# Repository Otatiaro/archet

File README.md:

# Archet

Open-source debug and production-test probe, and hardware-in-the-loop (HIL) platform.

- SWD and JTAG with **reliable simultaneous SWO**, on separate hardware paths;
- ARM, RISC-V and ESP32 (Xtensa) targets;
- USB HS (USB-C, PD) and 100 Mbit/s Ethernet with PoE+, IEEE 1588 clock synchronisation;
- HIL platform: real-time rules on raw IOs (≤ 1 µs), edge timestamping, safe state; each project only adds a simple shield, or [Bornier](https://github.com/bornier-dev/bornier) modules;
- host side: probe-rs, CMSIS-DAP v2 compatibility, Rust/Python library and MCP server.

Built around an STM32H723 and a Lattice iCE40UP5K, manufacturable at JLCPCB with no BGA.

**Status:** architecture draft, no hardware yet.

## Documentation

- [Architecture](docs/architecture.md): goals, decisions, block diagram, MCU ↔ FPGA link, power, pinout constraints, sourcing and cost.

## Related projects

- [OpSy](https://github.com/Otatiaro/OpSy): firmware runtime (C++26);
- [SvdGenerator](https://github.com/Otatiaro/SvdGenerator): register headers;
- [Bornier](https://github.com/bornier-dev/bornier): DIN-rail IO modules, shared local bus.

## Contributing

All content in this repository is in English: code, comments, documentation, commit messages and pull requests.

## License

[MIT](LICENSE), hardware, gateware, firmware and software alike.

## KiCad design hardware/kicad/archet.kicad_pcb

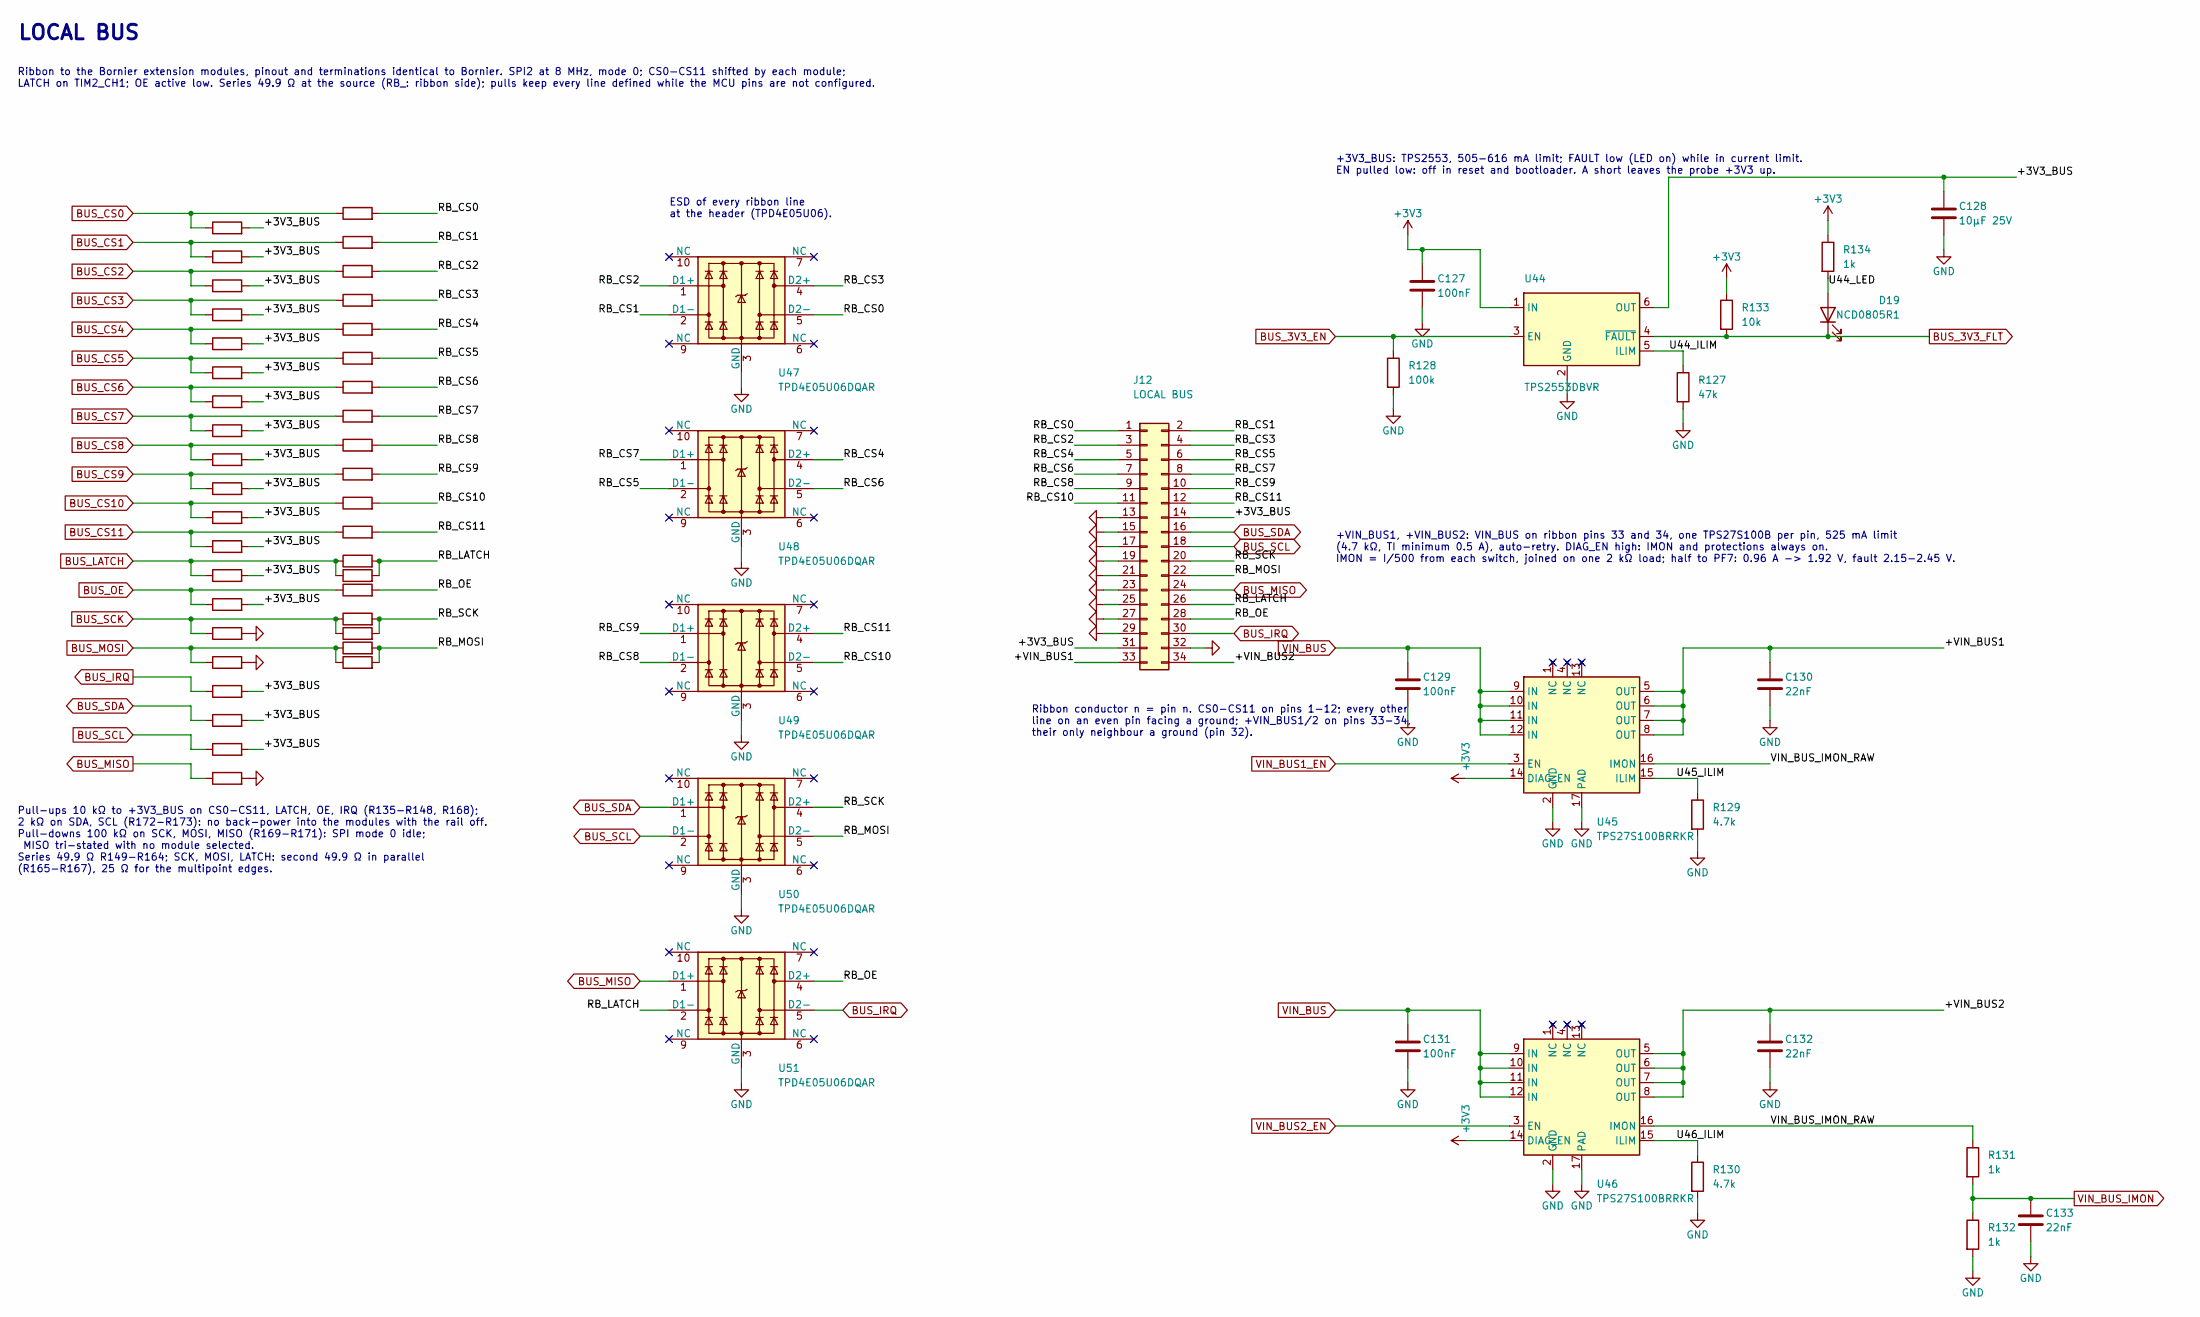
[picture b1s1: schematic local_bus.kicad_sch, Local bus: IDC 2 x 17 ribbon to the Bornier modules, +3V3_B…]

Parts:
C127, C129, C131: 100nF; C_0402_1005Metric; LCSC C307331
C128: 10µF 25V; C_0805_2012Metric; LCSC C15850
C130, C132, C133: 22nF; C_0402_1005Metric; LCSC C1532
D19: NCD0805R1; LED_0805_2012Metric; LCSC C84256
J12: LOCAL BUS; IDC-Header_2x17_P2.54mm_Vertical; LCSC C20920
R127: 47k; R_0402_1005Metric; LCSC C25792
R128, R169, R170, R171: 100k; R_0402_1005Metric; LCSC C25741
R129, R130: 4.7k; R_0402_1005Metric; LCSC C25900
R131, R132, R134: 1k; R_0402_1005Metric; LCSC C11702
R133, R135, R136, R137, R138, R139, R140, R141, R142, R143, R144, R145, R146, R147, R148, R168: 10k; R_0402_1005Metric; LCSC C25744
R149, R150, R151, R152, R153, R154, R155, R156, R157, R158, R159, R160, R161, R162, R163, R164, R165, R166, R167: 49.9; R_0402_1005Metric; LCSC C25120
R172, R173: 2k; R_0402_1005Metric; LCSC C4109
U44: TPS2553DBVR; SOT-23-6; LCSC C55266
U45, U46: TPS27S100BRRKR; Texas_RRK0016A_WQFN-16-1EP_3.5x4mm_P0.5mm_EP2.05x2.55mm; LCSC C1849486
U47, U48, U49, U50, U51: TPD4E05U06DQAR; USON-10_2.5x1.0mm_P0.5mm; LCSC C138714

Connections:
+3V3: C127.1, R133.1, R134.1, U44.1 (IN), U45.14 (DIAG_EN), U46.14 (DIAG_EN); also elsewhere on the board
/Local bus/+3V3_BUS: C128.1, J12.14, J12.31, R135.2, R136.2, R137.2, R138.2, R139.2, R140.2, R141.2, R142.2, R143.2, R144.2, R145.2, R146.2, R147.2, R148.2, R168.2, R172.2, R173.2, U44.6 (OUT)
/Local bus/+VIN_BUS1: C130.1, J12.33, U45.5 (OUT), U45.6 (OUT), U45.7 (OUT), U45.8 (OUT)
/Local bus/+VIN_BUS2: C132.1, J12.34, U46.5 (OUT), U46.6 (OUT), U46.7 (OUT), U46.8 (OUT)
/Local bus/RB_CS0: J12.1, R149.2, U47.5 (D2-)
/Local bus/RB_CS1: J12.2, R150.2, U47.2 (D1-)
/Local bus/RB_CS2: J12.3, R151.2, U47.1 (D1+)
/Local bus/RB_CS3: J12.4, R152.2, U47.4 (D2+)
/Local bus/RB_CS4: J12.5, R153.2, U48.4 (D2+)
/Local bus/RB_CS5: J12.6, R154.2, U48.2 (D1-)
/Local bus/RB_CS6: J12.7, R155.2, U48.5 (D2-)
/Local bus/RB_CS7: J12.8, R156.2, U48.1 (D1+)
/Local bus/RB_CS8: J12.9, R157.2, U49.2 (D1-)
/Local bus/RB_CS9: J12.10, R158.2, U49.1 (D1+)
/Local bus/RB_CS10: J12.11, R159.2, U49.5 (D2-)
/Local bus/RB_CS11: J12.12, R160.2, U49.4 (D2+)
/Local bus/RB_LATCH: J12.26, R163.2, R167.2, U51.2 (D1-)
/Local bus/RB_MOSI: J12.22, R162.2, R166.2, U50.5 (D2-)
/Local bus/RB_OE: J12.28, R164.2, U51.4 (D2+)
/Local bus/RB_SCK: J12.20, R161.2, R165.2, U50.4 (D2+)
/Local bus/U44_ILIM: R127.1, U44.5 (ILIM)
/Local bus/U44_LED: D19.2 (A), R134.2
/Local bus/U45_ILIM: R129.1, U45.15 (ILIM)
/Local bus/U46_ILIM: R130.1, U46.15 (ILIM)
/Local bus/VIN_BUS_IMON_RAW: R131.1, U45.16 (IMON), U46.16 (IMON)
BUS_3V3_EN: R128.1, U44.3 (EN); also elsewhere on the board
BUS_3V3_FLT: D19.1 (K), R133.2, U44.4 (~FAULT); also elsewhere on the board
BUS_CS0: R135.1, R149.1; also elsewhere on the board
BUS_CS1: R136.1, R150.1; also elsewhere on the board
BUS_CS2: R137.1, R151.1; also elsewhere on the board
BUS_CS3: R138.1, R152.1; also elsewhere on the board
BUS_CS4: R139.1, R153.1; also elsewhere on the board
BUS_CS5: R140.1, R154.1; also elsewhere on the board
BUS_CS6: R141.1, R155.1; also elsewhere on the board
BUS_CS7: R142.1, R156.1; also elsewhere on the board
BUS_CS8: R143.1, R157.1; also elsewhere on the board
BUS_CS9: R144.1, R158.1; also elsewhere on the board
BUS_CS10: R145.1, R159.1; also elsewhere on the board
BUS_CS11: R146.1, R160.1; also elsewhere on the board
BUS_IRQ: J12.30, R168.1, U51.5 (D2-); also elsewhere on the board
BUS_LATCH: R147.1, R163.1, R167.1; also elsewhere on the board
BUS_MISO: J12.24, R169.1, U51.1 (D1+); also elsewhere on the board
BUS_MOSI: R162.1, R166.1, R171.1; also elsewhere on the board
BUS_OE: R148.1, R164.1; also elsewhere on the board
BUS_SCK: R161.1, R165.1, R170.1; also elsewhere on the board
BUS_SCL: J12.18, R173.1, U50.2 (D1-); also elsewhere on the board
BUS_SDA: J12.16, R172.1, U50.1 (D1+); also elsewhere on the board
GND: C127.2, C128.2, C129.2, C130.2, C131.2, C132.2, C133.2, J12.13, J12.15, J12.17, J12.19, J12.21, J12.23, J12.25, J12.27, J12.29, J12.32, R127.2, R128.2, R129.2, R130.2, R132.2, R169.2, R170.2, R171.2, U44.2 (GND), U45.2 (GND), U45.17 (PAD), U46.2 (GND), U46.17 (PAD), U47.3 (GND), U47.8 (GND), U48.3 (GND), U48.8 (GND), U49.3 (GND), U49.8 (GND), U50.3 (GND), U50.8 (GND), U51.3 (GND), U51.8 (GND); also elsewhere on the board
VIN_BUS: C129.1, C131.1, U45.9 (IN), U45.10 (IN), U45.11 (IN), U45.12 (IN), U46.9 (IN), U46.10 (IN), U46.11 (IN), U46.12 (IN); also elsewhere on the board
VIN_BUS1_EN: U45.3 (EN); also elsewhere on the board
VIN_BUS2_EN: U46.3 (EN); also elsewhere on the board
VIN_BUS_IMON: C133.1, R131.2, R132.1; also elsewhere on the board

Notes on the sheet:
LOCAL BUS
Ribbon to the Bornier extension modules, pinout and terminations identical to Bornier. SPI2 at 8 MHz, mode 0; CS0-CS11 shifted by each module; LATCH on TIM2_CH1; OE active low. Series 49.9 Ω at the source (RB_: ribbon side); pulls keep every line defined while the MCU pins are not configured.
Pull-ups 10 kΩ to +3V3_BUS on CS0-CS11, LATCH, OE, IRQ (R135-R148, R168); 2 kΩ on SDA, SCL (R172-R173): no back-power into the modules with the rail off. Pull-downs 100 kΩ on SCK, MOSI, MISO (R169-R171): SPI mode 0 idle; MISO tri-stated with no module selected. Series 49.9 Ω R149-R164; SCK, MOSI, L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
ESD of every ribbon line at the header (TPD4E05U06).
Ribbon conductor n = pin n. CS0-CS11 on pins 1-12; every other line on an even pin facing a ground; +VIN_BUS1/2 on pins 33-34, their only neighbour a ground (pin 32).
+3V3_BUS: TPS2553, 505-616 mA limit; FAULT low (LED on) while in current limit. EN pulled low: off in reset and bootloader. A short leaves the probe +3V3 up.
+VIN_BUS1, +VIN_BUS2: VIN_BUS on ribbon pins 33 and 34, one TPS27S100B per pin, 525 mA limit (4.7 kΩ, TI minimum 0.5 A), auto-retry. DIAG_EN high: IMON and protections always on. IMON = I/500 from each switch, joined on one 2 kΩ load; half to PF7: 0.96 A -> 1.92 V, fault 2.15-2.45 V.

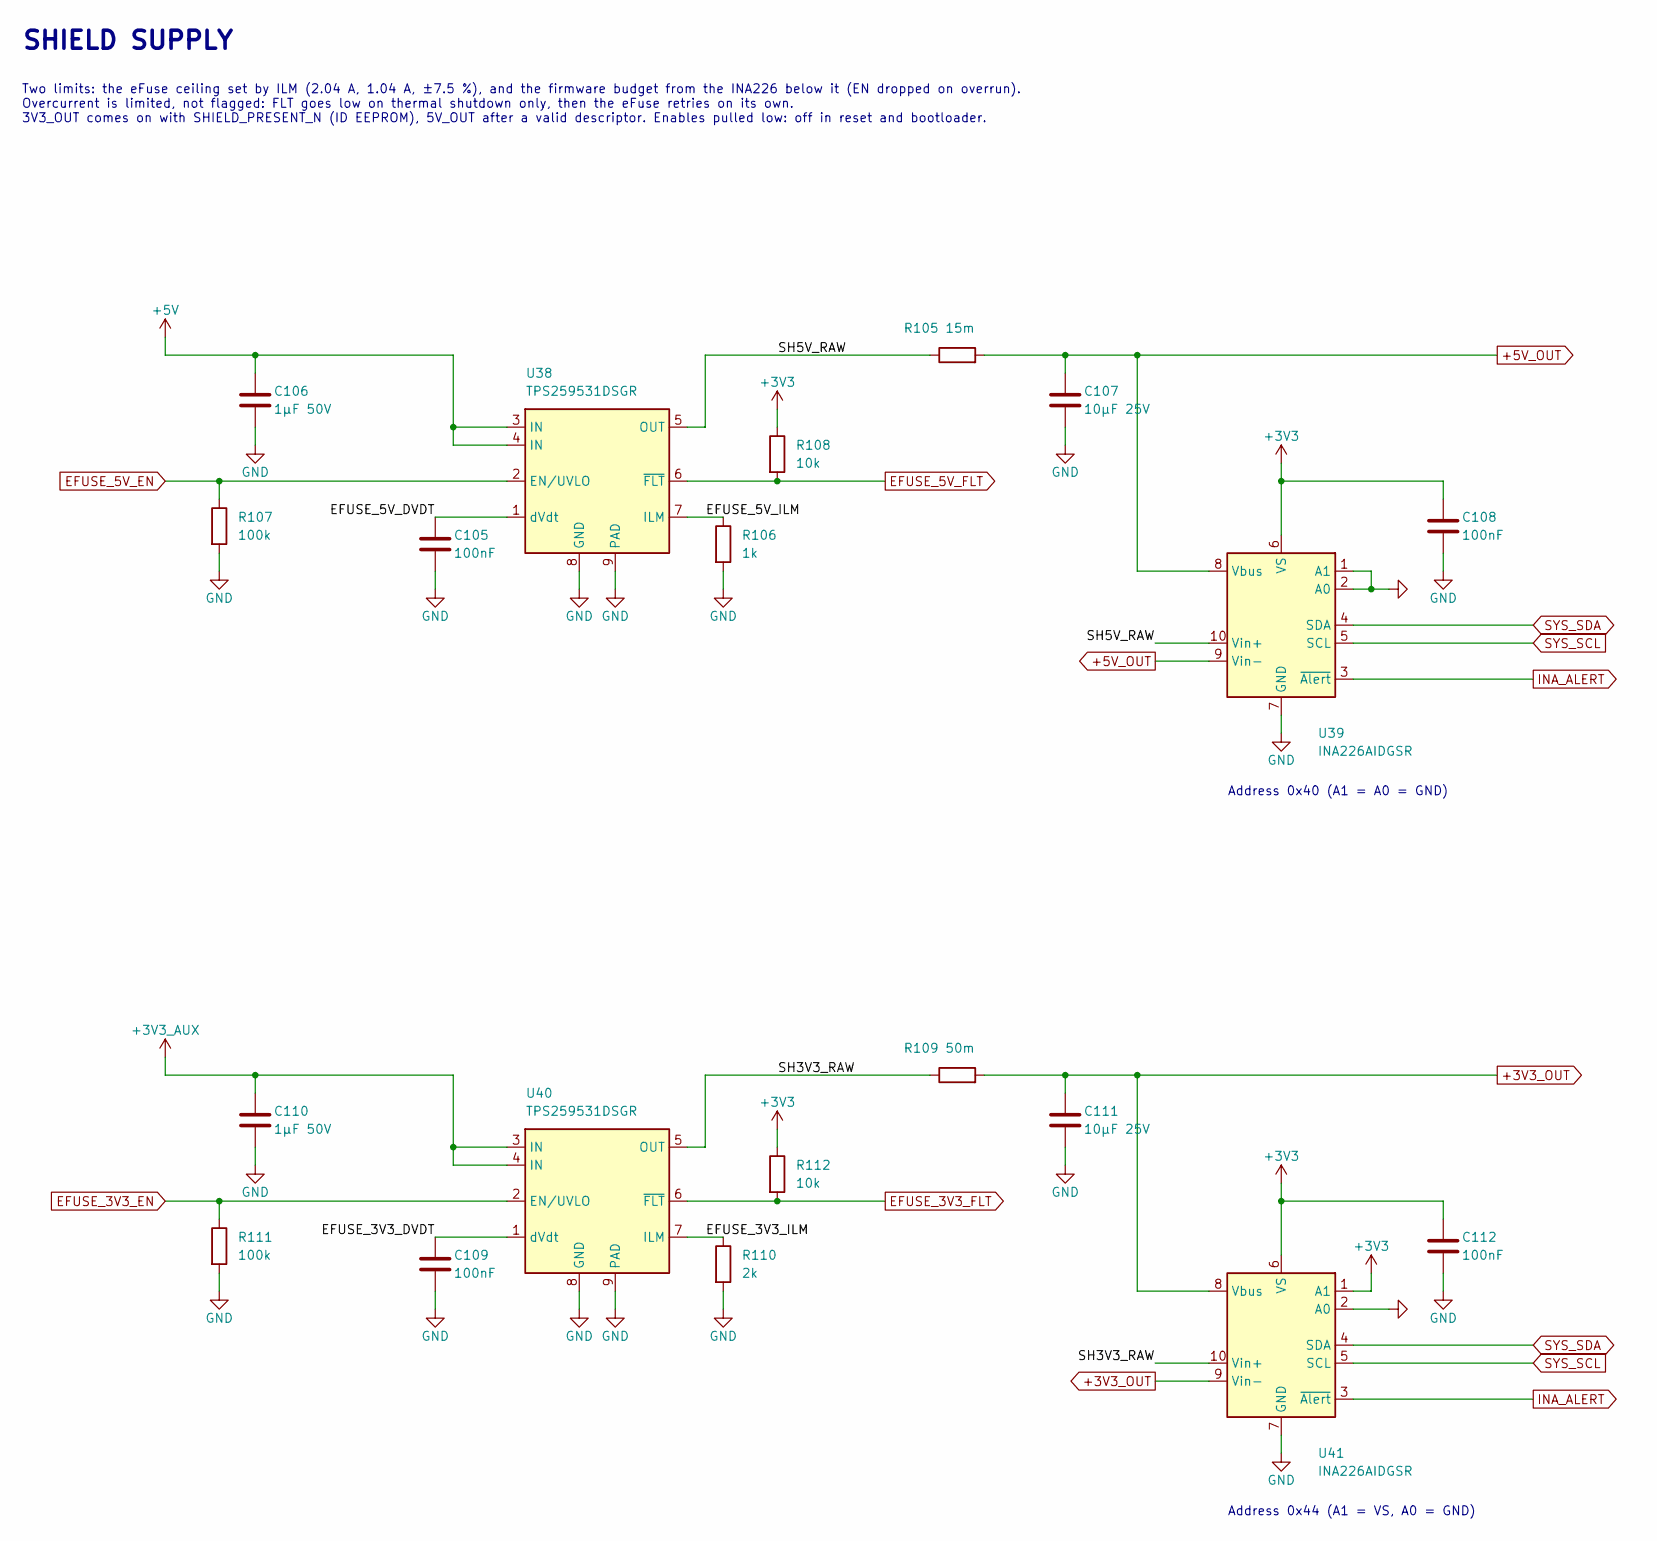
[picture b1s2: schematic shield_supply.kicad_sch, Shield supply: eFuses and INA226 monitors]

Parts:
C105, C108, C109, C112: 100nF; C_0402_1005Metric; LCSC C307331
C106, C110: 1µF 50V; C_0603_1608Metric; LCSC C15849
C107, C111: 10µF 25V; C_0805_2012Metric; LCSC C15850
R105: 15m; R_1206_3216Metric; LCSC C844483
R106: 1k; R_0402_1005Metric; LCSC C11702
R107, R111: 100k; R_0402_1005Metric; LCSC C25741
R108, R112: 10k; R_0402_1005Metric; LCSC C25744
R109: 50m; R_1206_3216Metric; LCSC C844686
R110: 2k; R_0402_1005Metric; LCSC C4109
U38, U40: TPS259531DSGR; Texas_DSG0008A_WSON-8-1EP_2x2mm_P0.5mm_EP0.9x1.6mm; LCSC C2155674
U39, U41: INA226AIDGSR; TSSOP-10_3x3mm_P0.5mm; LCSC C49851

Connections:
+3V3: C108.1, C112.1, R108.1, R112.1, U39.6 (VS), U41.1 (A1), U41.6 (VS); also elsewhere on the board
+3V3_AUX: C110.1, U40.3 (IN), U40.4 (IN); also elsewhere on the board
+3V3_OUT: C111.1, R109.2, U41.8 (Vbus), U41.9 (Vin-); also elsewhere on the board
+5V: C106.1, U38.3 (IN), U38.4 (IN); also elsewhere on the board
+5V_OUT: C107.1, R105.2, U39.8 (Vbus), U39.9 (Vin-); also elsewhere on the board
/Shield supply/EFUSE_3V3_DVDT: C109.1, U40.1 (dVdt)
/Shield supply/EFUSE_3V3_ILM: R110.1, U40.7 (ILM)
/Shield supply/EFUSE_5V_DVDT: C105.1, U38.1 (dVdt)
/Shield supply/EFUSE_5V_ILM: R106.1, U38.7 (ILM)
/Shield supply/SH3V3_RAW: R109.1, U40.5 (OUT), U41.10 (Vin+)
/Shield supply/SH5V_RAW: R105.1, U38.5 (OUT), U39.10 (Vin+)
EFUSE_3V3_EN: R111.1, U40.2 (EN/UVLO); also elsewhere on the board
EFUSE_3V3_FLT: R112.2, U40.6 (~FLT); also elsewhere on the board
EFUSE_5V_EN: R107.1, U38.2 (EN/UVLO); also elsewhere on the board
EFUSE_5V_FLT: R108.2, U38.6 (~FLT); also elsewhere on the board
GND: C105.2, C106.2, C107.2, C108.2, C109.2, C110.2, C111.2, C112.2, R106.2, R107.2, R110.2, R111.2, U38.8 (GND), U38.9 (PAD), U39.1 (A1), U39.2 (A0), U39.7 (GND), U40.8 (GND), U40.9 (PAD), U41.2 (A0), U41.7 (GND); also elsewhere on the board
INA_ALERT: U39.3 (~Alert), U41.3 (~Alert); also elsewhere on the board
SYS_SCL: U39.5 (SCL), U41.5 (SCL); also elsewhere on the board
SYS_SDA: U39.4 (SDA), U41.4 (SDA); also elsewhere on the board

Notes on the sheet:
SHIELD SUPPLY
Two limits: the eFuse ceiling set by ILM (2.04 A, 1.04 A, ±7.5 %), and the firmware budget from the INA226 below it (EN dropped on overrun). Overcurrent is limited, not flagged: FLT goes low on thermal shutdown only, then the eFuse retries on its own. 3V3_OUT comes on with SHIELD_PRESENT_N (ID EEPR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
Address 0x40 (A1 = A0 = GND)
Address 0x44 (A1 = VS, A0 = GND)

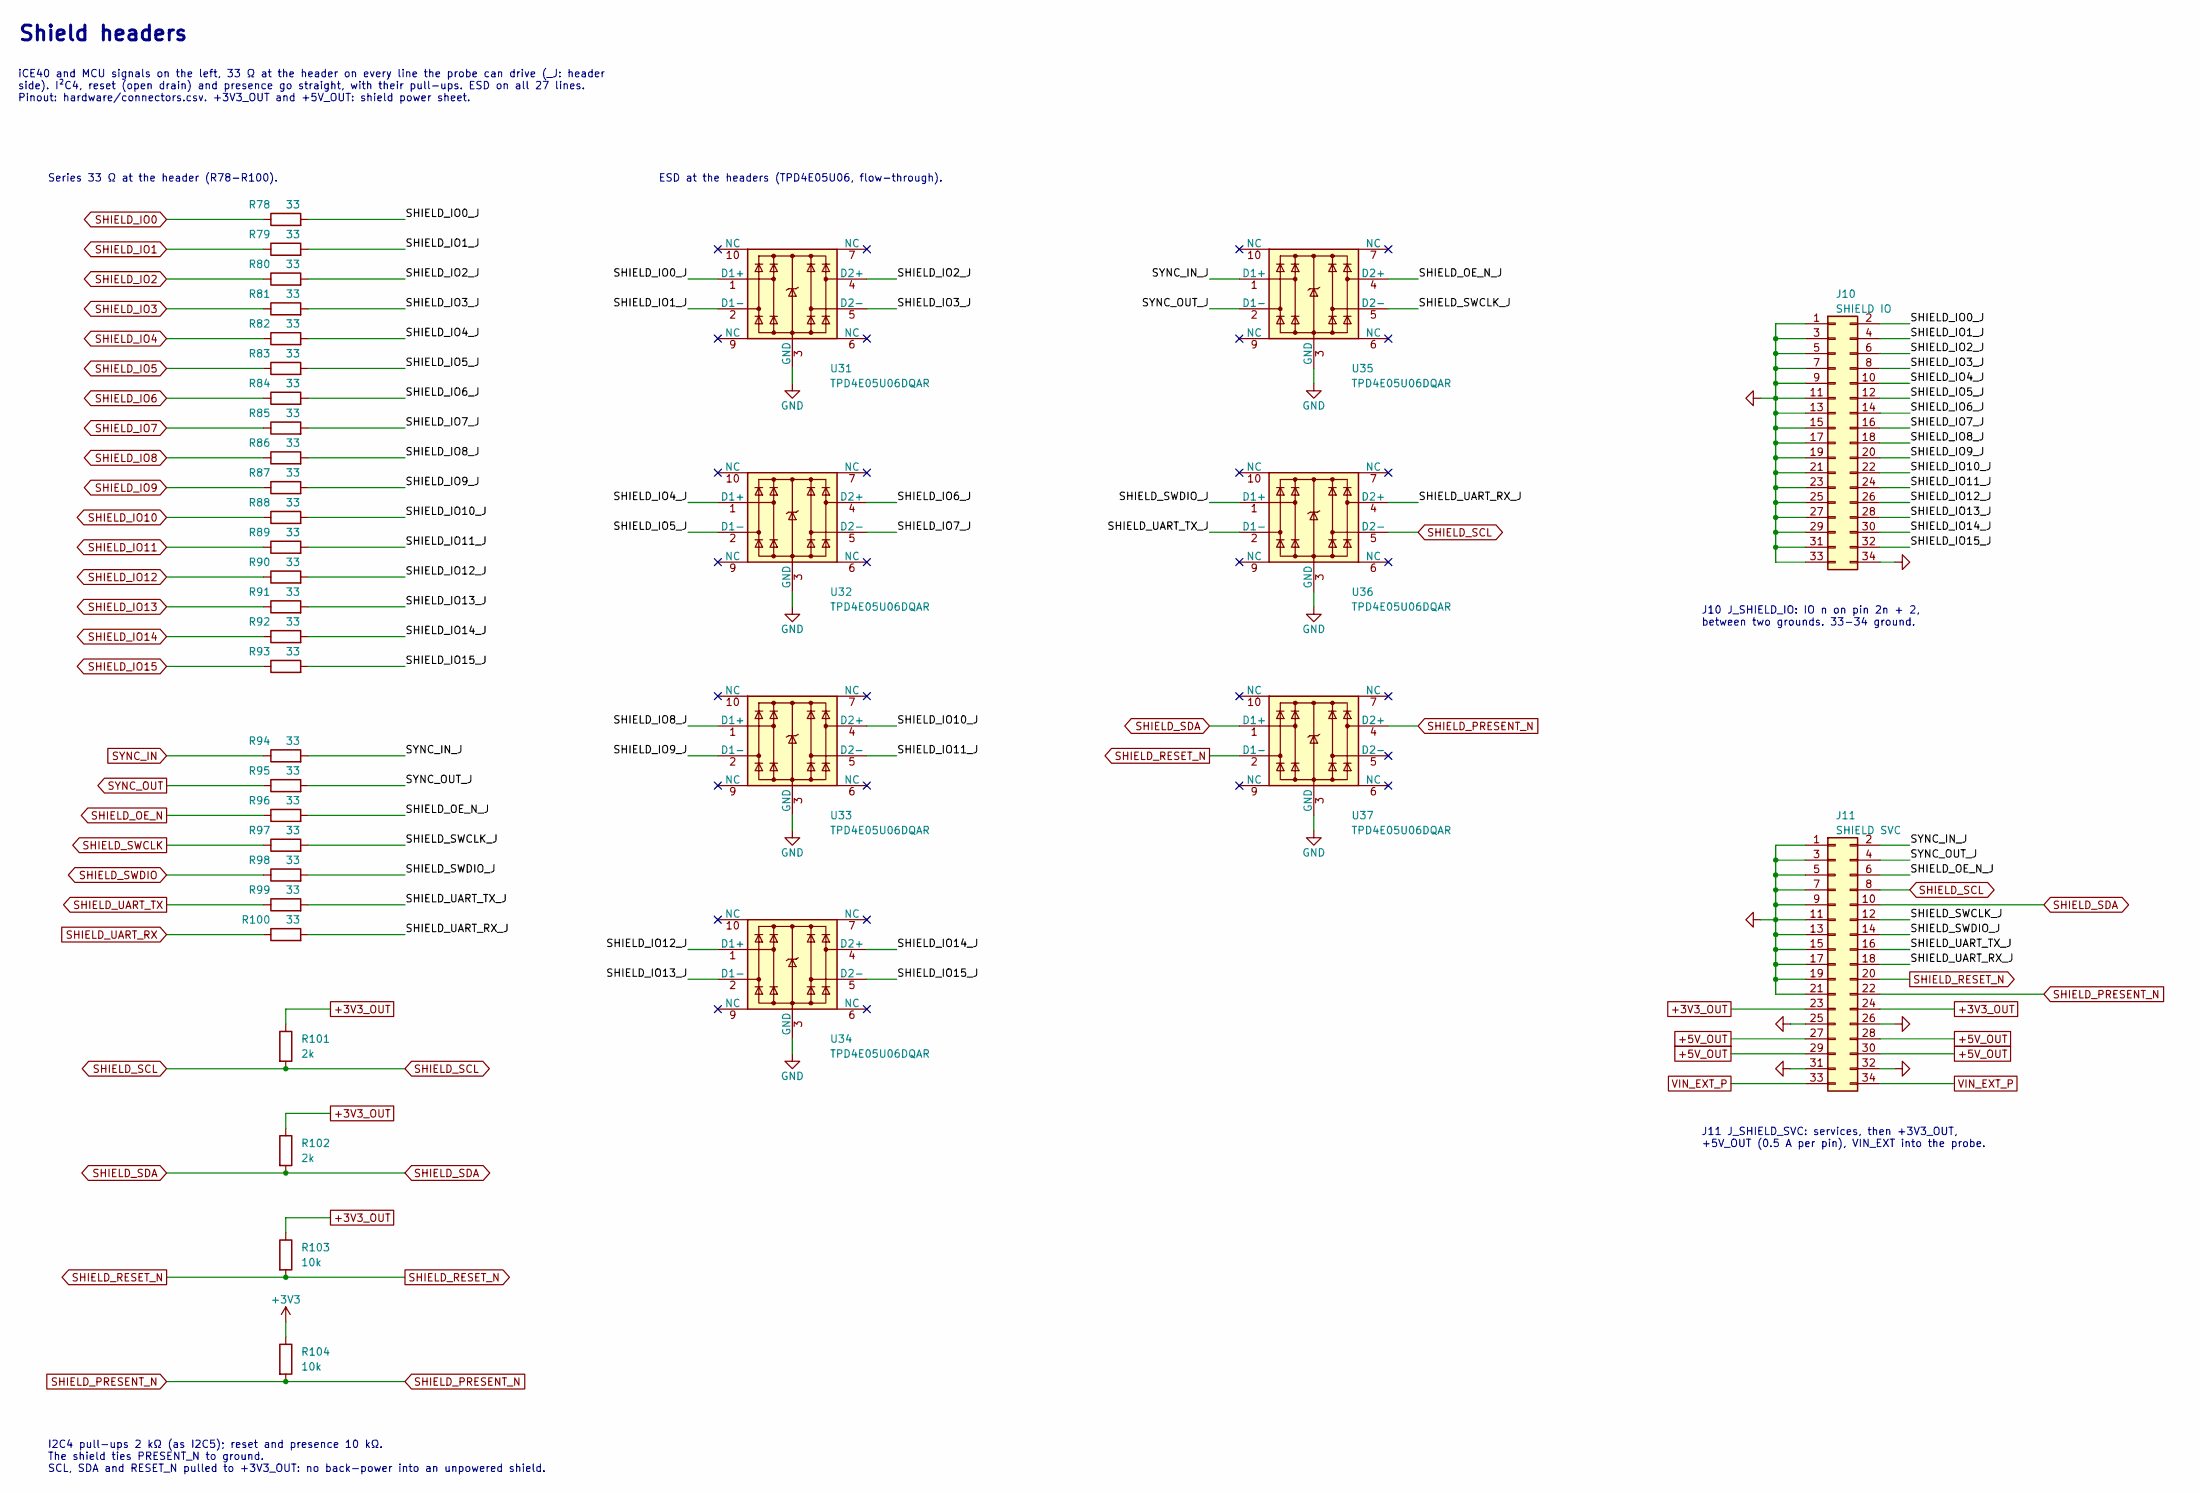
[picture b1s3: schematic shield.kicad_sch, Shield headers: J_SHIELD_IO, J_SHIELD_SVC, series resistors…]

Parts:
J10: SHIELD IO; IDC-Header_2x17_P2.54mm_Vertical; LCSC C20920
J11: SHIELD SVC; IDC-Header_2x17_P2.54mm_Vertical; LCSC C20920
R78, R79, R80, R81, R82, R83, R84, R85, R86, R87, R88, R89, R90, R91, R92, R93, R94, R95, R96, R97, R98, R99, R100: 33; R_0402_1005Metric; LCSC C25105
R101, R102: 2k; R_0402_1005Metric; LCSC C4109
R103, R104: 10k; R_0402_1005Metric; LCSC C25744
U31, U32, U33, U34, U35, U36, U37: TPD4E05U06DQAR; USON-10_2.5x1.0mm_P0.5mm; LCSC C138714

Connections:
+3V3: R104.1; also elsewhere on the board
+3V3_OUT: J11.23, J11.24, R101.1, R102.1, R103.1; also elsewhere on the board
+5V_OUT: J11.27, J11.28, J11.29, J11.30; also elsewhere on the board
/Shield/SHIELD_IO0_J: J10.2, R78.2, U31.1 (D1+)
/Shield/SHIELD_IO1_J: J10.4, R79.2, U31.2 (D1-)
/Shield/SHIELD_IO2_J: J10.6, R80.2, U31.4 (D2+)
/Shield/SHIELD_IO3_J: J10.8, R81.2, U31.5 (D2-)
/Shield/SHIELD_IO4_J: J10.10, R82.2, U32.1 (D1+)
/Shield/SHIELD_IO5_J: J10.12, R83.2, U32.2 (D1-)
/Shield/SHIELD_IO6_J: J10.14, R84.2, U32.4 (D2+)
/Shield/SHIELD_IO7_J: J10.16, R85.2, U32.5 (D2-)
/Shield/SHIELD_IO8_J: J10.18, R86.2, U33.1 (D1+)
/Shield/SHIELD_IO9_J: J10.20, R87.2, U33.2 (D1-)
/Shield/SHIELD_IO10_J: J10.22, R88.2, U33.4 (D2+)
/Shield/SHIELD_IO11_J: J10.24, R89.2, U33.5 (D2-)
/Shield/SHIELD_IO12_J: J10.26, R90.2, U34.1 (D1+)
/Shield/SHIELD_IO13_J: J10.28, R91.2, U34.2 (D1-)
/Shield/SHIELD_IO14_J: J10.30, R92.2, U34.4 (D2+)
/Shield/SHIELD_IO15_J: J10.32, R93.2, U34.5 (D2-)
/Shield/SHIELD_OE_N_J: J11.6, R96.2, U35.4 (D2+)
/Shield/SHIELD_SWCLK_J: J11.12, R97.2, U35.5 (D2-)
/Shield/SHIELD_SWDIO_J: J11.14, R98.2, U36.1 (D1+)
/Shield/SHIELD_UART_RX_J: J11.18, R100.2, U36.4 (D2+)
/Shield/SHIELD_UART_TX_J: J11.16, R99.2, U36.2 (D1-)
/Shield/SYNC_IN_J: J11.2, R94.2, U35.1 (D1+)
/Shield/SYNC_OUT_J: J11.4, R95.2, U35.2 (D1-)
GND: J10.1, J10.3, J10.5, J10.7, J10.9, J10.11, J10.13, J10.15, J10.17, J10.19, J10.21, J10.23, J10.25, J10.27, J10.29, J10.31, J10.33, J10.34, J11.1, J11.3, J11.5, J11.7, J11.9, J11.11, J11.13, J11.15, J11.17, J11.19, J11.21, J11.25, J11.26, J11.31, J11.32, U31.3 (GND), U31.8 (GND), U32.3 (GND), U32.8 (GND), U33.3 (GND), U33.8 (GND), U34.3 (GND), U34.8 (GND), U35.3 (GND), U35.8 (GND), U36.3 (GND), U36.8 (GND), U37.3 (GND), U37.8 (GND); also elsewhere on the board
SHIELD_IO0: R78.1; also elsewhere on the board
SHIELD_IO1: R79.1; also elsewhere on the board
SHIELD_IO2: R80.1; also elsewhere on the board
SHIELD_IO3: R81.1; also elsewhere on the board
SHIELD_IO4: R82.1; also elsewhere on the board
SHIELD_IO5: R83.1; also elsewhere on the board
SHIELD_IO6: R84.1; also elsewhere on the board
SHIELD_IO7: R85.1; also elsewhere on the board
SHIELD_IO8: R86.1; also elsewhere on the board
SHIELD_IO9: R87.1; also elsewhere on the board
SHIELD_IO10: R88.1; also elsewhere on the board
SHIELD_IO11: R89.1; also elsewhere on the board
SHIELD_IO12: R90.1; also elsewhere on the board
SHIELD_IO13: R91.1; also elsewhere on the board
SHIELD_IO14: R92.1; also elsewhere on the board
SHIELD_IO15: R93.1; also elsewhere on the board
SHIELD_OE_N: R96.1; also elsewhere on the board
SHIELD_PRESENT_N: J11.22, R104.2, U37.4 (D2+); also elsewhere on the board
SHIELD_RESET_N: J11.20, R103.2, U37.2 (D1-); also elsewhere on the board
SHIELD_SCL: J11.8, R101.2, U36.5 (D2-); also elsewhere on the board
SHIELD_SDA: J11.10, R102.2, U37.1 (D1+); also elsewhere on the board
SHIELD_SWCLK: R97.1; also elsewhere on the board
SHIELD_SWDIO: R98.1; also elsewhere on the board
SHIELD_UART_RX: R100.1; also elsewhere on the board
SHIELD_UART_TX: R99.1; also elsewhere on the board
SYNC_IN: R94.1; also elsewhere on the board
SYNC_OUT: R95.1; also elsewhere on the board
VIN_EXT_P: J11.33, J11.34; also elsewhere on the board

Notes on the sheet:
Shield headers
iCE40 and MCU signals on the left, 33 Ω at the header on every line the probe can drive (_J: header side). I²C4, reset (open drain) and presence go straight, with their pull-ups. ESD on all 27 lines. Pinout: hardware/connectors.csv. +3V3_OUT and +5V_OUT: shield power sheet.
Series 33 Ω at the header (R78-R100).
I2C4 pull-ups 2 kΩ (as I2C5); reset and presence 10 kΩ. The shield ties PRESENT_N to ground. SCL, SDA and RESET_N pulled to +3V3_OUT: no back-power into an unpowered shield.
ESD at the headers (TPD4E05U06, flow-through).
J10 J_SHIELD_IO: IO n on pin 2n + 2, between two grounds. 33-34 ground.
J11 J_SHIELD_SVC: services, then +3V3_OUT, +5V_OUT (0.5 A per pin), VIN_EXT into the probe.

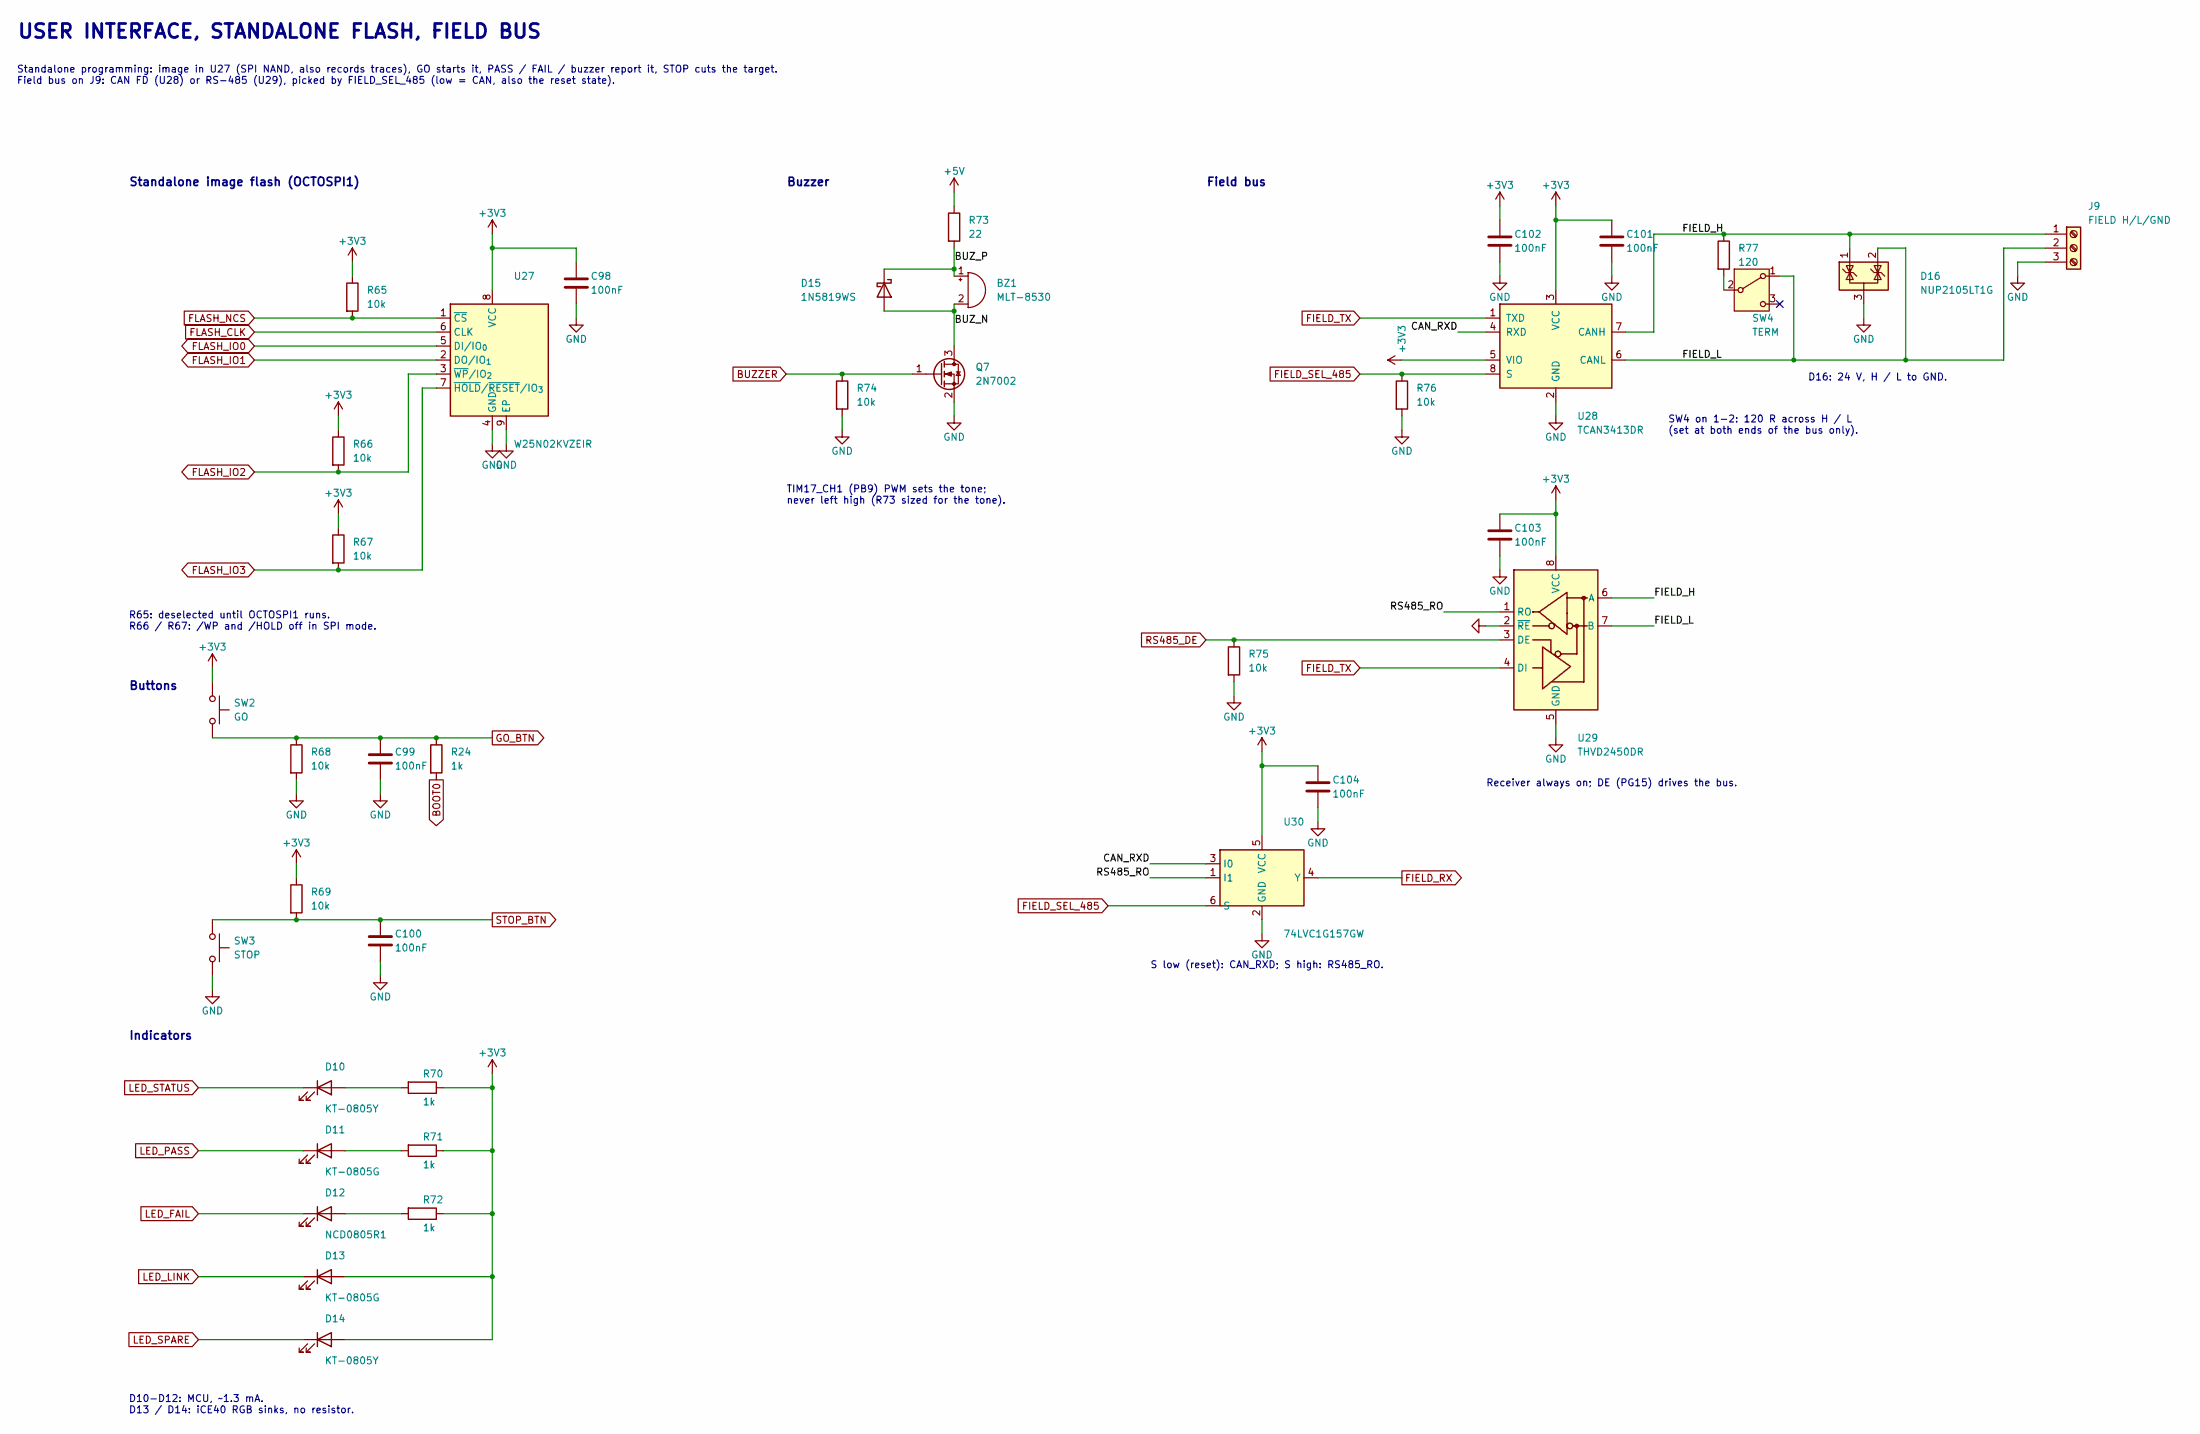
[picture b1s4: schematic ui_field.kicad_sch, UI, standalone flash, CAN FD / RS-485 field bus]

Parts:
BZ1: MLT-8530; Buzzer_HNDZ_MLT-8530; LCSC C94599
C98, C99, C100, C101, C102, C103, C104: 100nF; C_0402_1005Metric; LCSC C307331
D10, D14: KT-0805Y; LED_0805_2012Metric; LCSC C2296
D11, D13: KT-0805G; LED_0805_2012Metric; LCSC C2297
D12: NCD0805R1; LED_0805_2012Metric; LCSC C84256
D15: 1N5819WS; D_SOD-323; LCSC C191023
D16: NUP2105LT1G; SOT-23; LCSC C14486
J9: FIELD H/L/GND; PhoenixContact_MC_1,5_3-G-3.81_1x03_P3.81mm_Horizontal; LCSC C441183
Q7: 2N7002; SOT-23; LCSC C8545
R24, R70, R71, R72: 1k; R_0402_1005Metric; LCSC C11702
R65, R66, R67, R68, R69, R74, R75, R76: 10k; R_0402_1005Metric; LCSC C25744
R73: 22; R_1206_3216Metric; LCSC C17958
R77: 120; R_0603_1608Metric; LCSC C22787
SW2: GO; SW_Push_1P1T_XKB_TS-1187A; LCSC C318884
SW3: STOP; SW_Push_1P1T_XKB_TS-1187A; LCSC C318884
SW4: TERM; SW_SPDT_Shouhan_MSK12C02; LCSC C431540
U27: W25N02KVZEIR; WSON-8-1EP_8x6mm_P1.27mm_EP3.4x4.3mm; LCSC C17626844
U28: TCAN3413DR; SOIC-8_3.9x4.9mm_P1.27mm; LCSC C22433320
U29: THVD2450DR; SOIC-8_3.9x4.9mm_P1.27mm; LCSC C2672621
U30: 74LVC1G157GW; SOT-363_SC-70-6; LCSC C135822

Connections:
+3V3: C98.1, C101.1, C102.1, C103.1, C104.1, D13.2 (A), D14.2 (A), R65.1, R66.1, R67.1, R69.1, R70.1, R71.1, R72.1, SW2.1, U27.8 (VCC), U28.3 (VCC), U28.5 (VIO), U29.8 (VCC), U30.5 (VCC); also elsewhere on the board
+5V: R73.1; also elsewhere on the board
/UI and field bus/BUZ_N: BZ1.2 (-), D15.2 (A), Q7.3 (D)
/UI and field bus/BUZ_P: BZ1.1 (+), D15.1 (K), R73.2
/UI and field bus/CAN_RXD: U28.4 (RXD), U30.3 (I0)
/UI and field bus/FIELD_H: D16.1 (K), J9.1, R77.1, U28.7 (CANH), U29.6 (A)
/UI and field bus/FIELD_L: D16.2 (K), J9.2, SW4.1 (A), U28.6 (CANL), U29.7 (B)
/UI and field bus/RS485_RO: U29.1 (RO), U30.1 (I1)
BOOT0: R24.2; also elsewhere on the board
BUZZER: Q7.1 (G), R74.1; also elsewhere on the board
FIELD_RX: U30.4 (Y); also elsewhere on the board
FIELD_SEL_485: R76.1, U28.8 (S), U30.6 (S); also elsewhere on the board
FIELD_TX: U28.1 (TXD), U29.4 (DI); also elsewhere on the board
FLASH_CLK: U27.6 (CLK); also elsewhere on the board
FLASH_IO0: U27.5 (DI/IO_{0}); also elsewhere on the board
FLASH_IO1: U27.2 (DO/IO_{1}); also elsewhere on the board
FLASH_IO2: R66.2, U27.3 (~WP/IO_{2}); also elsewhere on the board
FLASH_IO3: R67.2, U27.7 (~HOLD/~RESET/IO_{3}); also elsewhere on the board
FLASH_NCS: R65.2, U27.1 (~CS); also elsewhere on the board
GND: C98.2, C99.2, C100.2, C101.2, C102.2, C103.2, C104.2, D16.3 (A), J9.3, Q7.2 (S), R68.2, R74.2, R75.2, R76.2, SW3.2, U27.4 (GND), U27.9 (EP), U28.2 (GND), U29.2 (~RE), U29.5 (GND), U30.2 (GND); also elsewhere on the board
GO_BTN: C99.1, R24.1, R68.1, SW2.2; also elsewhere on the board
LED_FAIL: D12.1 (K); also elsewhere on the board
LED_LINK: D13.1 (K); also elsewhere on the board
LED_PASS: D11.1 (K); also elsewhere on the board
LED_SPARE: D14.1 (K); also elsewhere on the board
LED_STATUS: D10.1 (K); also elsewhere on the board
unnamed: D10.2 (A), R70.2
unnamed: D11.2 (A), R71.2
unnamed: D12.2 (A), R72.2
unnamed: R77.2, SW4.2 (B)
RS485_DE: R75.1, U29.3 (DE); also elsewhere on the board
STOP_BTN: C100.1, R69.2, SW3.1; also elsewhere on the board

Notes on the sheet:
USER INTERFACE, STANDALONE FLASH, FIELD BUS
Standalone programming: image in U27 (SPI NAND, also records traces), GO starts it, PASS / FAIL / buzzer report it, STOP cuts the target. Field bus on J9: CAN FD (U28) or RS-485 (U29), picked by FIELD_SEL_485 (low = CAN, also the reset state).
Standalone image flash (OCTOSPI1)
R65: deselected until OCTOSPI1 runs. R66 / R67: /WP and /HOLD off in SPI mode.
Buttons
Indicators
D10-D12: MCU, ~1.3 mA. D13 / D14: iCE40 RGB sinks, no resistor.
Buzzer
TIM17_CH1 (PB9) PWM sets the tone; never left high (R73 sized for the tone).
Field bus
SW4 on 1-2: 120 R across H / L (set at both ends of the bus only).
D16: 24 V, H / L to GND.
Receiver always on; DE (PG15) drives the bus.
S low (reset): CAN_RXD; S high: RS485_RO.
